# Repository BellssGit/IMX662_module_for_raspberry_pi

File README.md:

# IMX662_module_for_raspberry_pi
A simple camera module for Raspberry Pi using IMX662 sensor

too lazy to adjust the focus, sorry.

[blog post](https://www.emoe.xyz/imx662_cam/)

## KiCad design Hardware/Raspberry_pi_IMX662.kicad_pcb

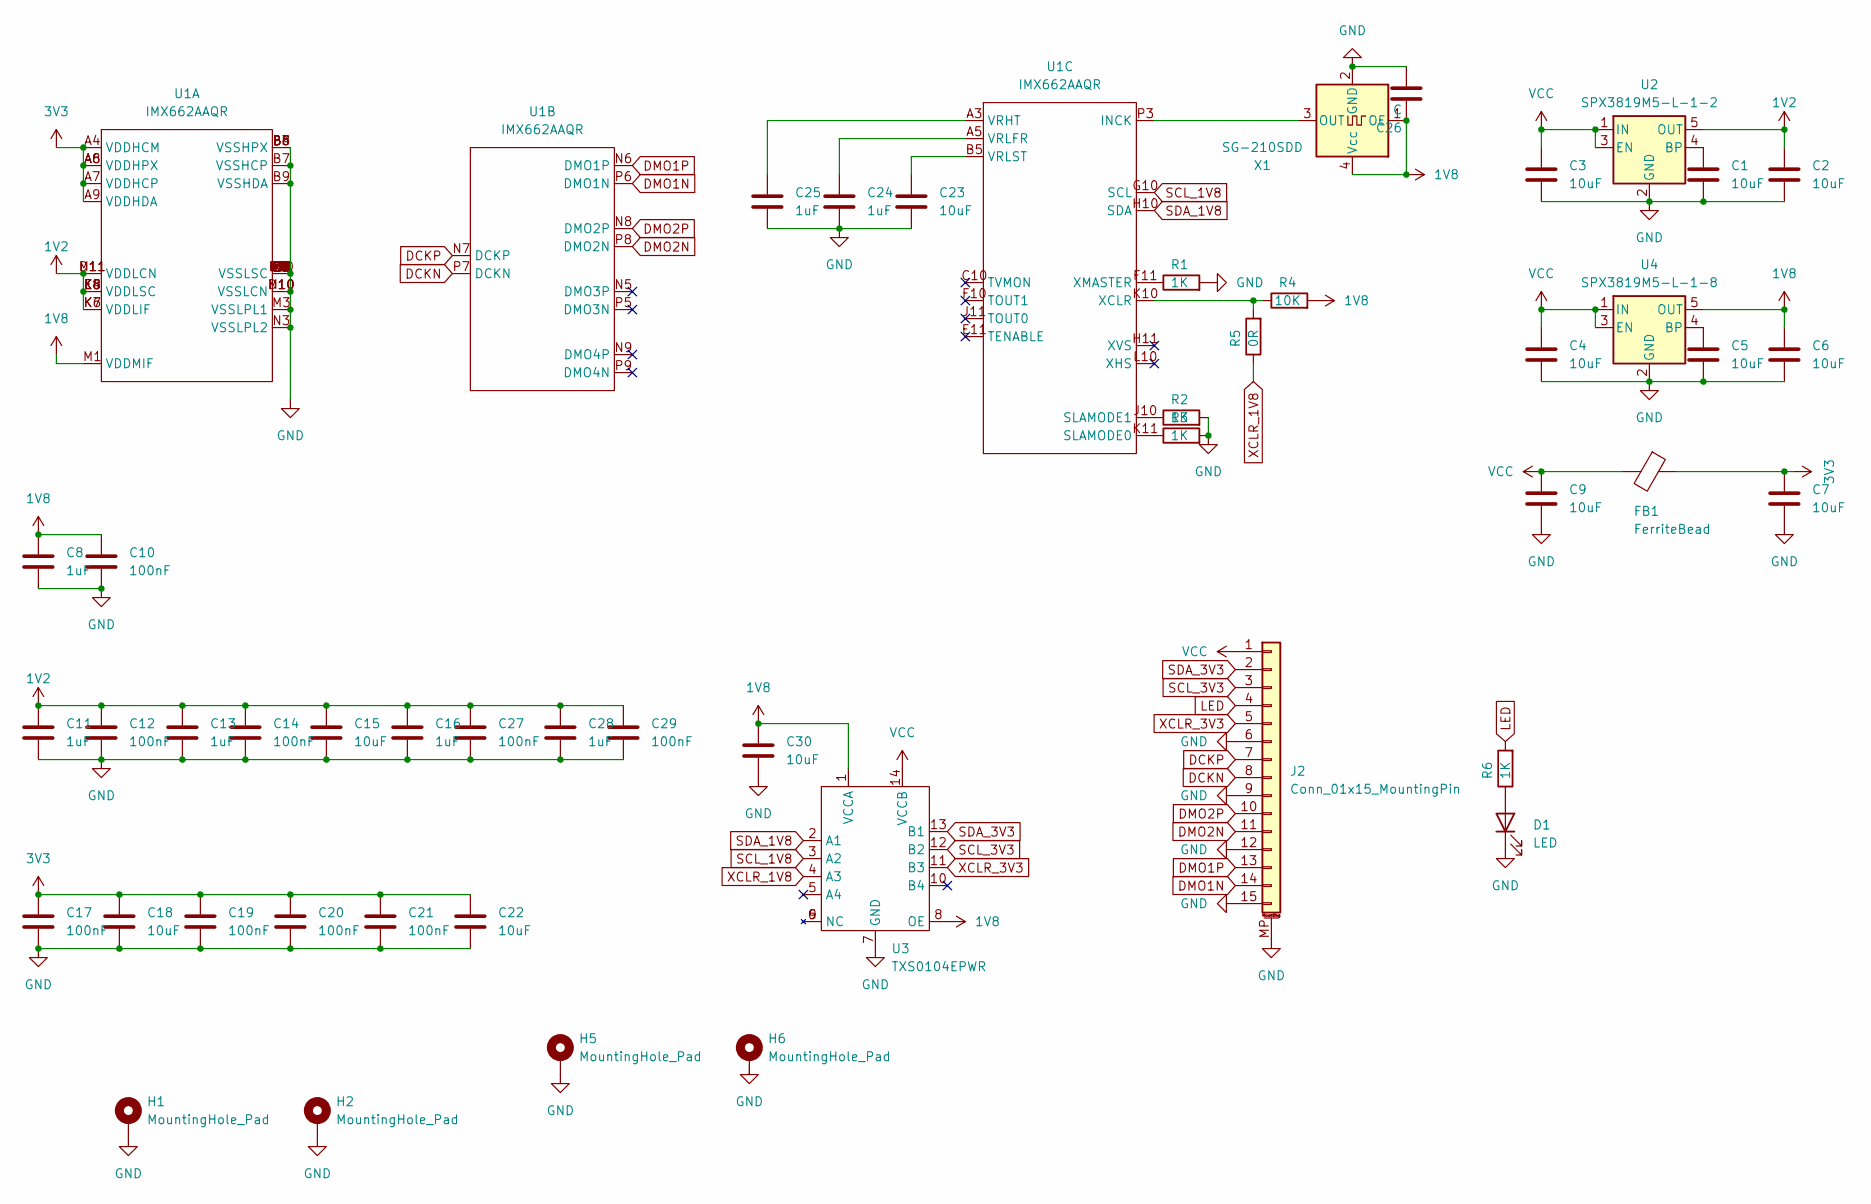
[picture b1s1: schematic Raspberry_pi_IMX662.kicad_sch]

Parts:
C1, C2, C3, C4, C5, C6, C7, C9, C15, C18, C22, C23, C30: 10uF; C_0603_1608Metric
C8, C11, C13, C16, C24, C25, C28: 1uF; C_0402_1005Metric
C10, C12, C14, C17, C19, C20, C21, C27, C29: 100nF; C_0402_1005Metric
C26: C; C_0603_1608Metric
D1: LED; LED_0603_1608Metric
FB1: FerriteBead; L_0805_2012Metric
H1, H2: MountingHole_Pad; MountingHole_2.2mm_M2_Pad
H5, H6: MountingHole_Pad; MountingHole_3.2mm_M3_Pad
J2: Conn_01x15_MountingPin; TE_1-84953-5_1x15-1MP_P1.0mm_Horizontal
R1, R2, R3, R6: 1K; R_0402_1005Metric
R4: 10K; R_0402_1005Metric
R5: 0R; R_0402_1005Metric
U1: IMX662AAQR; LGA-114_11x14_9.3x12.0mm
U2: SPX3819M5-L-1-2; SOT-23-5
U3: TXS0104EPWR; TSSOP-14_4.4x5mm_P0.65mm
U4: SPX3819M5-L-1-8; SOT-23-5
X1: SG-210SDD; Oscillator_SMD_Abracon_ASE-4Pin_3.2x2.5mm

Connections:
1V2: C2.1, C11.1, C12.1, C13.1, C14.1, C15.1, C16.1, C27.1, C28.1, C29.1, U1.D11 (VDDLCN), U1.E4 (VDDLSC), U1.E8 (VDDLSC), U1.K5 (VDDLSC), U1.K6 (VDDLIF), U1.K7 (VDDLIF), U1.K8 (VDDLSC), U1.M11 (VDDLCN), U2.5 (OUT)
1V8: C6.1, C8.1, C10.1, C26.1, C30.1, R4.2, U1.M1 (VDDMIF), U3.1 (VCCA), U3.8 (OE), U4.5 (OUT), X1.1 (OE), X1.4 (Vcc)
3V3: C7.1, C17.1, C18.1, C19.1, C20.1, C21.1, C22.1, FB1.1, U1.A4 (VDDHCM), U1.A6 (VDDHPX), U1.A7 (VDDHCP), U1.A8 (VDDHPX), U1.A9 (VDDHDA)
DCKN: J2.8, U1.P7 (DCKN)
DCKP: J2.7, U1.N7 (DCKP)
DMO1N: J2.14, U1.P6 (DMO1N)
DMO1P: J2.13, U1.N6 (DMO1P)
DMO2N: J2.11, U1.P8 (DMO2N)
DMO2P: J2.10, U1.N8 (DMO2P)
GND: C1.2, C2.2, C3.2, C4.2, C5.2, C6.2, C7.2, C8.2, C9.2, C10.2, C11.2, C12.2, C13.2, C14.2, C15.2, C16.2, C17.2, C18.2, C19.2, C20.2, C21.2, C22.2, C23.1, C24.2, C25.2, C26.2, C27.2, C28.2, C29.2, C30.2, D1.1 (K), H1.1, H2.1, H5.1, J2.6, J2.9, J2.12, J2.15, J2.MP (MountPin), R1.2, R2.2, R3.2, U1.B3 (VSSHPX), U1.B4 (VSSHPX), U1.B6 (VSSHPX), U1.B7 (VSSHCP), U1.B8 (VSSHPX), U1.B9 (VSSHDA), U1.C3 (VSSLSC), U1.D3 (VSSLSC), U1.D4 (VSSLSC), U1.D8 (VSSLSC), U1.D10 (VSSLCN), U1.E3 (VSSLSC), U1.E10 (VSSLSC), U1.K3 (VSSLSC), U1.L3 (VSSLSC), U1.L5 (VSSLSC), U1.L6 (VSSLSC), U1.L7 (VSSLSC), U1.L8 (VSSLSC), U1.L11 (VSSLSC), U1.M2 (VSSLSC), U1.M3 (VSSLPL1), U1.M5 (VSSLSC), U1.M6 (VSSLSC), U1.M7 (VSSLSC), U1.M8 (VSSLSC), U1.M9 (VSSLSC), U1.M10 (VSSLCN), U1.N3 (VSSLPL2), U2.2 (GND), U3.7 (GND), U4.2 (GND), X1.2 (GND)
LED: J2.4, R6.2
unnamed: D1.2 (A), R6.1
unnamed: U1.P3 (INCK), X1.3 (OUT)
unnamed: R3.1, U1.K11 (SLAMODE0)
unnamed: R2.1, U1.J10 (SLAMODE1)
unnamed: C25.1, U1.A3 (VRHT)
unnamed: C24.1, U1.A5 (VRLFR)
unnamed: C23.2, U1.B5 (VRLST)
unnamed: R4.1, R5.2, U1.K10 (XCLR)
unnamed: R1.1, U1.F11 (XMASTER)
unnamed: C1.1, U2.4 (BP)
unnamed: C5.1, U4.4 (BP)
SCL_1V8: U1.G10 (SCL), U3.3 (A2)
SCL_3V3: J2.3, U3.12 (B2)
SDA_1V8: U1.H10 (SDA), U3.2 (A1)
SDA_3V3: J2.2, U3.13 (B1)
VCC: C3.1, C4.1, C9.1, FB1.2, J2.1, U2.1 (IN), U2.3 (EN), U3.14 (VCCB), U4.1 (IN), U4.3 (EN)
XCLR_1V8: R5.1, U3.4 (A3)
XCLR_3V3: J2.5, U3.11 (B3)

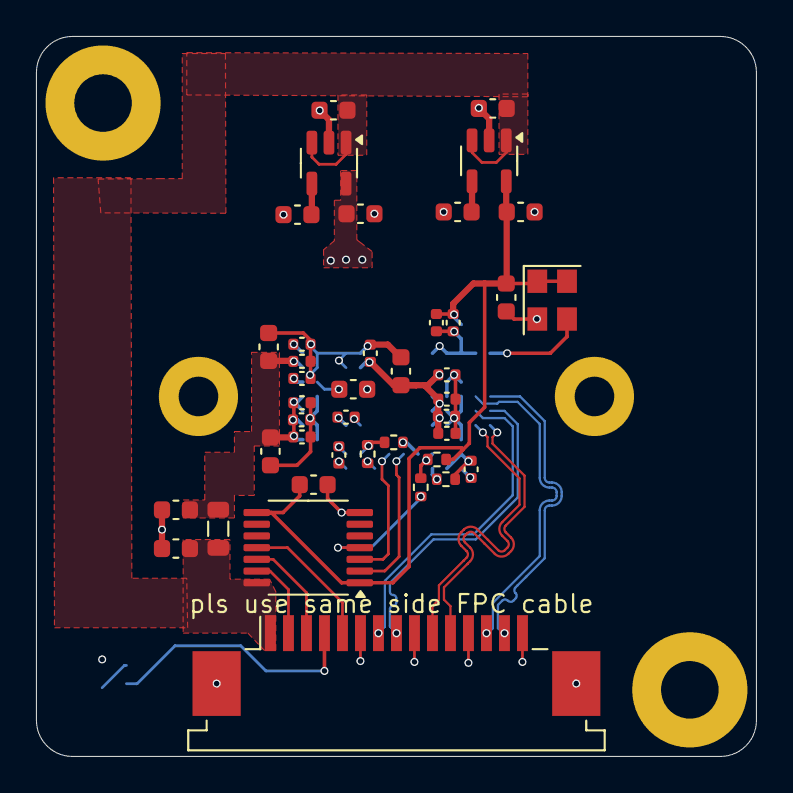
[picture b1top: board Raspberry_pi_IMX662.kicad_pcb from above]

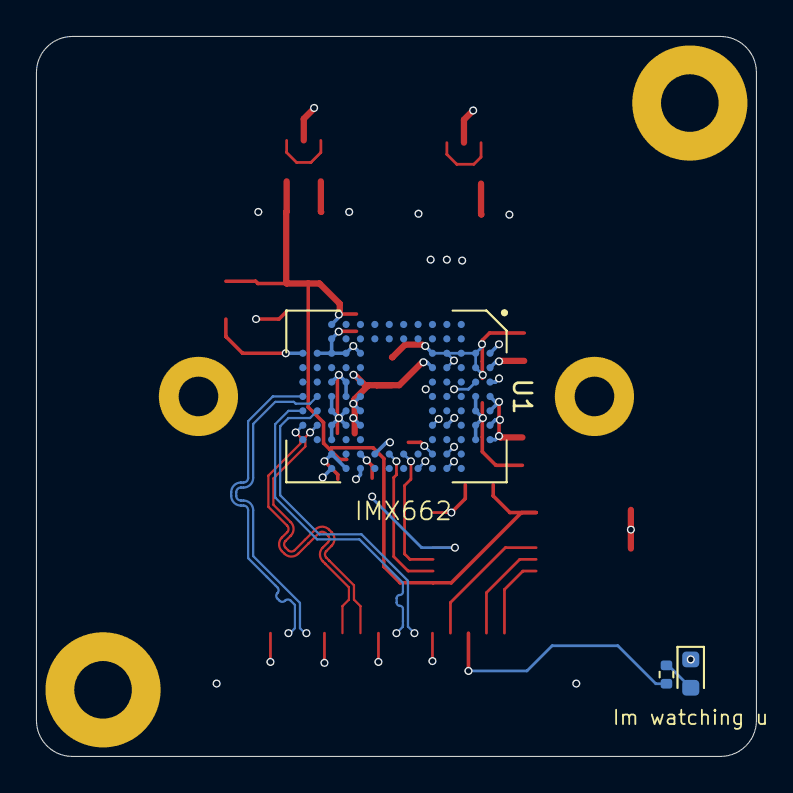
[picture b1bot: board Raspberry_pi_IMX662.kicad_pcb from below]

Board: 4 copper layers, 40.0 x 40.0 mm, 48 parts (3 on the bottom side), 29 nets.

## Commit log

2025-11-30 Add 2K60 mode settings and adjust probe function
